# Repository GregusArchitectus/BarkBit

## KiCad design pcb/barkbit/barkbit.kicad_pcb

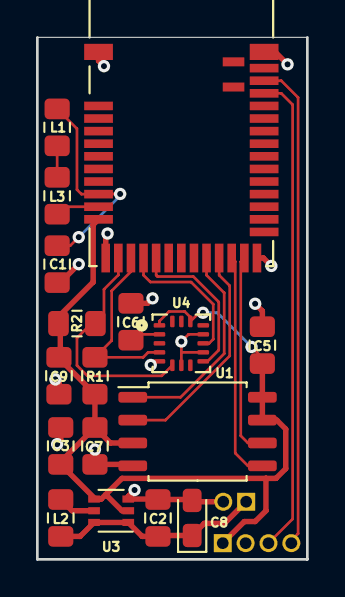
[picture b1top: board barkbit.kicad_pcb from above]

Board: 2 copper layers, 15.0 x 29.0 mm, 19 parts (0 on the bottom side), 18 nets.

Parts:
C1: 1uF; C_0805_2012Metric_Pad1.15x1.40mm_HandSolder
C2, C3, C9: 10uF; C_0805_2012Metric_Pad1.15x1.40mm_HandSolder
C5, C7: 4.7uf; C_0805_2012Metric_Pad1.15x1.40mm_HandSolder
C6: 0.1uf; C_0805_2012Metric_Pad1.15x1.40mm_HandSolder
C8: 47uf; CP_EIA-2012-12_Kemet-R_Pad1.30x1.05mm_HandSolder
J1: BATT; Wire_1x02_P1.27mm
J2: PRG; Wire_1x04_P1.27mm
L1: 15nH; L_0805_2012Metric_Pad1.15x1.40mm_HandSolder
L2: 4.7uH; L_0805_2012Metric_Pad1.15x1.40mm_HandSolder
L3: 10uH; L_0805_2012Metric_Pad1.15x1.40mm_HandSolder
R1, R2: 4.7k; R_0805_2012Metric_Pad1.15x1.40mm_HandSolder
U1: MX25R6435FM2IH0; SOIC-8_5.23x5.23mm_P1.27mm
U2: MDBT42Q; RAYTAC_MDBT42
U3: TLV61225; SOT-363_SC-70-6
U4: MMA8451Q; MMA845X_QFN_16MM

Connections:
+3V0: C2.2, C8.1, J1.1, L2.2, U3.1, U3.6
+3V3: C3.1, C5.1, C7.2, C9.2, J2.1, R1.2, R2.2, U1.3, U1.7, U1.8, U2.11, U3.2, U3.4, U4.1, U4.14
/FLASH_CS: U1.1, U2.20
/I2C_SCL: R1.1, U2.14, U4.4
/I2C_SDA: R2.1, U2.13, U4.6
/MMA_INT1: U2.15, U4.11
/MMA_INT2: U2.16, U4.9
/SPI_MISO: U1.2, U2.21
/SPI_MOSI: U1.5, U2.22
/SPI_SCK: U1.6, U2.23
/SWDCLK: J2.3, U2.36
/SWDIO: J2.4, U2.37
GND: C1.2, C2.1, C3.2, C5.2, C6.2, C7.1, C8.2, C9.1, J1.2, J2.2, U1.4, U2.1, U2.12, U2.24, U2.39, U3.3, U4.5, U4.7, U4.10, U4.12
unnamed: C1.1, L1.2, U2.9
unnamed: C6.1, U4.2
unnamed: L1.1, L3.2
unnamed: L2.1, U3.5
unnamed: L3.1, U2.10

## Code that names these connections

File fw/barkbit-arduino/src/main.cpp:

#include <Adafruit_MMA8451.h>
#include <Arduino.h>
#include <SEGGER_RTT.h>

#include "barkbit.h"
#include "bluefruit.h"
#include <Adafruit_LittleFS.h>
#include <InternalFileSystem.h>

using namespace Adafruit_LittleFS_Namespace;

#define rwrite_string SEGGER_RTT_WriteString
#define rprintf SEGGER_RTT_printf

#define PIN_MMA_INT1 2
#define PIN_MMA_INT2 3
#define PIN_FLASH_CS 7

Adafruit_MMA8451 mma = Adafruit_MMA8451();
SoftwareTimer ble_push;

BLEDis bledis;

transient_cfg_t transient_cfg{
    .x_enabled = true, .y_enabled = true, .z_enabled = true, .debounce_count = 1, .threshold = 10
};
uint32_t steps = 0;
bool update = false;

void save_cfg();

void threshold_write_cb(uint16_t conn_hdl, BLECharacteristic *chr, uint8_t *data, uint16_t len) {
  if (*data != transient_cfg.threshold) {
    transient_cfg.threshold = *data;
    mma.setTransientConfiguration(&transient_cfg);
    save_cfg();
    rprintf(0, "threshold_write_cb: %d\n", *data);
  }
}

void debounce_write_cb(uint16_t conn_hdl, BLECharacteristic *chr, uint8_t *data, uint16_t len) {
  if (*data != transient_cfg.debounce_count) {
    transient_cfg.debounce_count = *data;
    mma.setTransientConfiguration(&transient_cfg);
    save_cfg();
    rprintf(0, "debounce_write_cb: %d\n", *data);
  }
}

void setup_bb_svc() {
  bb_service.begin();

  bb_steps.setUserDescriptor("Steps");
  bb_steps.setProperties(CHR_PROPS_READ | CHR_PROPS_NOTIFY);
  bb_steps.setPermission(SECMODE_OPEN, SECMODE_NO_ACCESS);
  bb_steps.setFixedLen(sizeof(steps));
  bb_steps.begin();
  bb_steps.write32(steps);

  bb_threshold.setUserDescriptor("Threshold");
  bb_threshold.setProperties(CHR_PROPS_READ | CHR_PROPS_WRITE);
  bb_threshold.setPermission(SECMODE_OPEN, SECMODE_OPEN);
  bb_threshold.setFixedLen(1);
  bb_threshold.setWriteCallback(threshold_write_cb);
  bb_threshold.begin();
  bb_threshold.write8(transient_cfg.threshold);

  bb_debounce.setUserDescriptor("Debounce");
  bb_debounce.setProperties(CHR_PROPS_READ | CHR_PROPS_WRITE);
  bb_debounce.setPermission(SECMODE_OPEN, SECMODE_OPEN);
  bb_debounce.setFixedLen(1);
  bb_debounce.setWriteCallback(debounce_write_cb);
  bb_debounce.begin();
  bb_debounce.write8(transient_cfg.debounce_count);
}

void init_ble() {
  Bluefruit.begin();
  Bluefruit.configPrphBandwidth(BANDWIDTH_LOW);
  Bluefruit.autoConnLed(false);
  Bluefruit.setTxPower(0);  
  Bluefruit.setName("BarkBit");
  
  bledis.setManufacturer("Gregus Archetectus");
  bledis.setModel("BarkBit 1");
  bledis.begin();

  setup_bb_svc();

  Bluefruit.Advertising.addFlags(BLE_GAP_ADV_FLAGS_LE_ONLY_GENERAL_DISC_MODE);
  Bluefruit.Advertising.addTxPower();
  Bluefruit.Advertising.addService(bb_service);
  Bluefruit.ScanResponse.addName();

  Bluefruit.Advertising.restartOnDisconnect(true);
  Bluefruit.Advertising.setInterval(200 / .625, 1000 / .625);
  Bluefruit.Advertising.setFastTimeout(5);  // number of seconds in fast mode
  Bluefruit.Advertising.start(0);  // 0 = Don't stop advertising after n seconds
}

void log() {
  mma.read();
  char buf[50];
  sprintf(buf, "MMA->Xg:%f\tYg:%f\tZg:%f.\n", mma.x_g, mma.y_g, mma.z_g);
  rwrite_string(0, buf);
}

void trans() {
  update = true;
  rwrite_string(0, "-------------------------------------------STEP-----\n");
  log();
  steps++;
}

void ble_push_cb(TimerHandle_t t) {
  if (update) {
    update = false;
    rwrite_string(0, "ble_push_cb\n");
    bb_steps.notify32(steps);
  }
}

const uint16_t cfg_size = 2;
const char *cfg_filename = "/bb.cfg";
void save_cfg() {
  File cfg_file(InternalFS);
  cfg_file.open(cfg_filename, FILE_O_WRITE);
  cfg_file.seek(0);
  cfg_file.write(transient_cfg.threshold);
  cfg_file.write(transient_cfg.debounce_count);
  cfg_file.close();
}

void load_cfg() {
  File cfg_file(InternalFS);
  cfg_file.open(cfg_filename, FILE_O_READ);
  if (!cfg_file || cfg_file.size() != cfg_size) {
    if (cfg_file) {
      rprintf(0, "Invalid config size of %d. Resetting.\n", cfg_file.size());
      InternalFS.remove(cfg_filename);
    } else {
      rwrite_string(0, "Config file not found. Resetting.\n");
    }
    save_cfg();
  } else {
    cfg_file.readBytes(&transient_cfg.threshold, 1);
    cfg_file.readBytes(&transient_cfg.debounce_count, 1);
    cfg_file.close();
  }
}

void setup() {
  sd_power_dcdc_mode_set(NRF_POWER_DCDC_ENABLE);
  sd_power_mode_set(NRF_POWER_MODE_LOWPWR);

  pinMode(PIN_FLASH_CS, OUTPUT);
  digitalWrite(PIN_FLASH_CS, HIGH);

  InternalFS.begin();
  load_cfg();

  while (!mma.begin(0x1C, &transient_cfg)) {
    rprintf(0, "[%d]MMA8451: couldnt start\n", millis());
    delay(1000);
  }
  rprintf(0, "MMA8451 initialized with t:%d, d:%d!\n", transient_cfg.threshold, transient_cfg.debounce_count);

  Serial.end();

  // pinMode(PIN_MMA_INT1, INPUT_PULLUP);
  // attachInterrupt(digitalPinToInterrupt(PIN_MMA_INT1), log, FALLING);

  init_ble();

  pinMode(PIN_MMA_INT2, INPUT_PULLUP);
  attachInterrupt(digitalPinToInterrupt(PIN_MMA_INT2), trans, FALLING);

  ble_push.begin(5000, ble_push_cb);
  ble_push.start();

  suspendLoop();
}

void loop() {}

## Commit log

2020-06-24 Initial checkin.
2020-06-24 Complete schematic.
2020-07-05 Final board. Cleanups.
2020-07-09 Cleanups.
2020-07-12 Reorg ref a bit.
2020-07-12 R1 of fw. * Somewhat working Arduino version that pushes messages to ble UART. * Not at all working Zephyr prototype.
2020-07-18 Reference cleanup and tweaks.
2020-07-18 Futzing around with zephyr.
2020-07-18 Move to local MMA library. Hack in tansient detection.
2020-07-18 Implement basic push of steps.
2020-07-19 Add support for configurable threshold and debounce.
2020-07-19 Write config to a file.
2020-08-14 Sorta finalish version for the first video.
